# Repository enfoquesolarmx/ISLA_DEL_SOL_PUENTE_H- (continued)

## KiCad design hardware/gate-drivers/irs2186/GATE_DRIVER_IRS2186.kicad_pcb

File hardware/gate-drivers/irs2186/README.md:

# Módulo gate driver de medio puente H con IRS2186

**Proyecto:** Puente H — prototipo SPWM "Isla del Sol" (inversor 48 V → 127 V / 60 Hz, 1000 W; modo cargador 1 kVA)
**Módulo:** gate driver de **medio puente H** (una rama: MOSFET alto + MOSFET bajo) con bootstrap. Es el **módulo principal de producción**: bajo costo y 500 ns de tiempo muerto
**Intercambiable con:** UCC21520DW y TLP250 de trinchera (misma interfaz J1/J5, mismo firmware)
**Estado:** diseño terminado con P9 en J1; esquemático reordenado por bloques (2026-11-12). Pendiente: DRC final, fabricación y validación en banco
**Fecha:** 2026-11-03 (esquemático por bloques: 2026-11-12)
**Documentos relacionados:** [`docs/identificacion_dt_pin9.md`](../../../docs/identificacion_dt_pin9.md), [`docs/compensacion_adaptativa_tiempo_muerto.md`](../../../docs/compensacion_adaptativa_tiempo_muerto.md), [módulo TLP250](../tlp250-trinchera/README.md)

> Verificar los valores marcados con *(verificar)* contra el esquemático de KiCad antes de fabricar.

| Cara de componentes | Cara de soldadura |
| --- | --- |
|  |  |

*Esquemático por bloques (KiCad 9, hoja A4): **A** entrada J1 con R1/R2 y P9 · **B** alimentación de 15 V · **C** IRS2186 · **D** bootstrap · **E** salida J5 y NT1 · **F** reglas de firmware y compras. Cada bloque lleva su nota de diseño.*

*Izquierda: arriba, la bornera J1 de entrada (**P**9 · GND · L · GND · H); en medio, el IRS2186 (SOIC-8) con su desacoplo de 15 V (1 µF + 10 µF), la red de bootstrap (2.2 Ω 1 W + ES1D), el zener D6 de 18 V (1SMA5931BT3G), los capacitores de bootstrap (2 × 10 µF) y el electrolítico de respaldo de 15 V; abajo, el header J5 hacia el puente H (HO · VS1 · · · Gk · LO · G · 15V · llave). Derecha: la leyenda de seguridad **"ATENCIÓN: DT 500 ns MIN — VALIDAR MOSFET Y SW"**, la versión V.0.1.NOV.26.J.G y la **X** de la llave en la posición 8 de J5.*

---

## 1. Qué maneja este módulo

Cada módulo maneja **una rama** del puente H: el **MOSFET del lado alto** (HO, referido a VS, alimentado por bootstrap) y el **MOSFET del lado bajo** (LO, referido a COM).

```
            +48 V
              │
     HA ──► [MOSFET alto]          [MOSFET alto] ◄── HB
              │                         │
              ├── VS1 ──► transformador ◄── VS2 ──┤
              │                         │
     LA ──► [MOSFET bajo]          [MOSFET bajo] ◄── LB
              │                         │
             GND ───────────────────── GND
         └── módulo rama A ──┘    └── módulo rama B ──┘
```

- **El puente completo usa dos módulos iguales:** rama A (VS1) y rama B (VS2). En la rama B, "H" y "L" de J1 manejan HB y LB, y el pin "VS1" de J5 va a VS2.
- **Inversor (modulación híbrida):** rama A a **24 kHz**, rama B a **60 Hz**.
- **Cargador (unipolar):** las dos ramas a **24 kHz**.
- **Alcance:** **1 IRF100P219 por posición** (o hasta 2 IRF540N) con 500 ns. Para más carga de compuerta hace falta tótem rápido o el módulo UCC21520 (ver sección 6).

### Por qué el IRS2186

| Criterio | IRS2186 (este) | UCC21520DW | TLP250 + tótem |
| --- | --- | --- | --- |
| Costo y número de componentes | **El menor** ✓ | Medio | El mayor |
| Tiempo muerto | **500 ns** ✓ | 500 ns | 1 µs |
| Corriente de salida | 4 A / 4 A | 4 A / 6 A | ~2 A (más con tótem) |
| Aislamiento entrada / potencia | **No** (lógica referida a COM) | Sí | Sí |
| Reparación a mano | SOIC-8 | SOIC-16 ancho | DIP y TO-220 |

---

## 2. Interfaz

### 2.1 J1 — entrada, hacia la tarjeta de control (bornera de 5 terminales)

| Terminal | Señal | En este módulo |
| --- | --- | --- |
| 1 | H | HIN del IRS2186 (con 10 kΩ a GND) |
| 2 | GND | Tierra lógica = COM (trenzar con H) |
| 3 | L | LIN del IRS2186 (con 10 kΩ a GND) |
| 4 | GND | Tierra lógica = COM (trenzar con L) |
| **5** | **P9 — ID DT** | **Unido a GND** → el MCU usa **500 ns** |

- Serigrafía: "TRENZAR H Y L CON GND", etiquetas H / GND / L / GND / P9. Recomendado agregar **"OPERACION DT IRS2186=500NS"**.
- Las resistencias de 10 kΩ de HIN y LIN a GND mantienen los MOSFET apagados si la tarjeta de control no está conectada o el MCU está en reset.
- Si P9 queda con soldadura fría o cable suelto, el MCU lee 1 → **1 µs** (falla segura: funciona con más armónicos).

### 2.2 J5 — salida, hacia la tarjeta del puente H (header de 9 posiciones, 2.54 mm)

| Pin | Señal | Nota |
| --- | --- | --- |
| 1 | HO | Compuerta lado alto |
| 2 | VS1 | Fuente lado alto (nodo de conmutación) |
| 3 | — | Libre (separación del nodo conmutado) |
| 4 | GND_K | Retorno Kelvin del lado bajo |
| 5 | LO | Compuerta lado bajo |
| 6 | GND | Tierra de potencia |
| 7 | 15 V | Alimentación |
| 8 | — | **Llave mecánica:** sin pad; **quitar el pin 8 del header**; "X" en serigrafía |
| 9 | GND | Reservado (no se lee) |

### 2.3 Tierras: la entrada comparte la tierra de potencia

En el IRS2186 la lógica (HIN, LIN) va referida a **COM**, que también es el retorno del lado bajo. Por eso **el GND de J1 es la misma tierra de potencia**: el módulo no aísla la tarjeta de control.

Consecuencias y cuidados:

1. **Lazo de tierra:** el GND del cable J1 es un camino más entre la tarjeta de control y la potencia; con dos módulos (rama A y B) ya hay dos. Parte de la corriente de conmutación puede circular por esos cables.
2. **Rebote de tierra:** el di/dt del MOSFET bajo puede mover COM unos cientos de mV respecto al GND del MCU. El IRS2186 tiene umbrales de entrada de ~0.8 V / ~2.5 V *(verificar en la hoja de datos)*; con MCU a 5 V el margen es mayor.
3. **Medidas:**
   - **Par trenzado H/GND y L/GND, lo más corto posible.**
   - **Un solo punto de unión** entre tierra de control y tierra de potencia en la tarjeta del puente H (estrella), cerca de la fuente del MOSFET bajo o del shunt.
   - **Retorno de LO hacia GND_K** (Kelvin) y lógica hacia GND, unidos en un solo punto: la corriente de compuerta no debe pasar por la tierra de las entradas.
4. Si en banco aparecen disparos falsos o ruido en las entradas, los módulos **UCC21520** o **TLP250** lo eliminan por diseño (entrada aislada).

---

## 3. Circuito

### 3.1 IRS2186 (SOIC-8)

| Pin | Señal | Conexión |
| --- | --- | --- |
| 1 | HIN | J1-H, 10 kΩ a GND |
| 2 | LIN | J1-L, 10 kΩ a GND |
| 3 | COM | GND (tierra lógica y retorno del lado bajo) |
| 4 | LO | J5-5 |
| 5 | VCC | 15 V, con desacoplo a COM |
| 6 | VS | J5-2 (VS1) |
| 7 | HO | J5-1 |
| 8 | VB | VB1, nodo del bootstrap |

Verificar contra la hoja de datos de la variante comprada (IRS2186S, SOIC-8).

**Datos de la hoja de datos (Infineon IRS2186):** salida 4 A / 4 A; retardo de propagación ~170 ns típ., 250 ns máx.; diferencia entre canales ≤ 35 ns; VCC 10–20 V; offset VS hasta 600 V *(verificar)*.

### 3.2 Alimentación de 15 V (lado bajo)

- 15 V desde J5-7 a VCC, con desacoplo **10 µF + 1 µF X7R** pegados a los pines 5 y 3, más capacitor electrolítico de respaldo en la línea de 15 V *(verificar valores)*.
- **¿Por qué 15 V y no 12 V?** Más voltaje de compuerta (menor R_DS(on) y más margen de UVLO en el bootstrap de la rama de 60 Hz) dentro del rango de VCC del IRS2186 y del ±20 V de V_GS del MOSFET.

### 3.3 Bootstrap (lado alto)

```
15 V ── D5 (ES1D / ES1J) ── R9 2.2 Ω 1 W ──┬── VB1 (pin 8)
                                           ├── C2 + C9: 2 × 10 µF X7R 50 V 1206 ── VS1
                                           └── D6 zener 18 V (1SMA5931BT3G), cátodo a VB1 ── VS1
```

| Componente | Valor | Por qué |
| --- | --- | --- |
| R9 | 2.2 Ω, 1 W, **después del diodo** (entre el cátodo de D5 y VB1) | Limita el pico de recarga del bootstrap cuando VS cae a 0 V y, en esta posición, también la corriente de recuperación inversa de D5 cuando VS sube (IR Design Tip DT98-2; TI SLUA887A; patente US5969964, ya expirada). La resistencia en serie con el diodo cumple igual antes o después de él |
| D5 | ES1D (200 V) o **ES1J (600 V)** | Diodo **ultrarrápido** (no Schottky). ES1D limita el bus del módulo a ~120 V; con ES1J el límite lo ponen las separaciones del PCB (≤ 150 V) |
| C2, C9 | 2 × 10 µF X7R 50 V 1206 | Sostiene VB durante los **8.3 ms** de encendido continuo de la rama de 60 Hz. El X7R pierde capacidad con el voltaje DC: por eso dos |
| D6 | Zener 18 V (1SMA5931BT3G), cátodo a VB1 | Protege VB–VS contra picos por encima del máximo del IRS2186 |

**Reglas de firmware para el bootstrap:**
- **Precarga** de 0.5–2 ms con los lados bajos encendidos antes de arrancar el PWM.
- **Ciclo de trabajo máximo ≤ 95 %** en la rama de 24 kHz, para dejar tiempo de recarga en cada periodo.

### 3.4 Red de compuerta

Las resistencias de compuerta de cada MOSFET (arreglo R1/R2/R3) y las **10 kΩ de compuerta a fuente** están en la **tarjeta del puente H**, junto a cada MOSFET. El módulo solo entrega HO y LO.

---

## 4. Tiempo muerto: 500 ns

| Concepto | Valor |
| --- | --- |
| Diferencia de retardo entre canales del IRS2186 | ≤ 35 ns |
| Apagado del IRF100P219 en el peor caso (con la red de compuerta) | ~390 ns |
| **Piso de tiempo muerto** | **~390–425 ns → se usa 500 ns** |

- **Por qué no 1 µs siempre:** con 500 ns el 3er armónico es ~0.58 % y el THD ~0.81 %; con 1 µs, ~1.17 % y ~1.62 % (híbrida, 24 kHz, 1000 W, sin compensación).
- El tiempo muerto se aplica en **ambos flancos**, por firmware. El IRS2186 **no tiene tiempo muerto interno ni interbloqueo**: si el firmware enciende HIN y LIN a la vez, enciende los dos MOSFET.
- El MCU elige 500 ns **solo si P9 de los dos módulos está a GND** (ver `identificacion_dt_pin9.md`).

---

## 5. Layout

- **Dominio HV** (VB, VS1, HO, bootstrap, zener): **0.6 mm** al resto (regla `HV_a_LV`, IPC-2221 B2 para ≤ 150 V):
  ```
  (rule "HV_a_LV" (constraint clearance (min 0.6mm)) (condition "A.NetClass == 'HV' && B.NetClass != 'HV'"))
  ```
- Capacitores de bootstrap y zener **pegados a los pines 8 y 6** del IRS2186; desacoplo de VCC pegado a los pines 5 y 3.
- J1: P9 y las dos GND unidos a la zona de GND. Recomendado: *Thermal reliefs* en esos pads para soldar la bornera a mano sin soldaduras frías.
- J5: sin pad 8 (llave) con "X" en serigrafía.

---

## 6. Alcance: cantidad de MOSFET por posición

### 6.1 Criterio

Con 500 ns de tiempo muerto y ≤ 35 ns de diferencia entre canales del IRS2186, el **apagado del MOSFET (o de los MOSFET en paralelo) debe quedar en ~400 ns como máximo**. El tiempo de apagado crece con la **carga de compuerta total** que el IRS2186 (4 A, ~3.75 Ω equivalentes a 15 V) tiene que sacar.

Referencia: **1 × IRF100P219 (~240 nC a 15 V) → ~390 ns**. Eso fija el presupuesto en **~250 nC por posición** sin ayuda externa.

| Carga de compuerta a 15 V | IRF100P219 | IRF540N | Sin ayuda (IRS2186 solo) | Con tótem rápido (D44H11/D45H11 o ZXTC2062E6) |
| --- | --- | --- | --- | --- |
| ~100 nC | — | 1 | ✓ amplio | ✓ |
| ~200 nC | — | 2 | ✓ | ✓ |
| ~240 nC | 1 | — | ✓ **(diseño actual)** | ✓ |
| ~300 nC | — | 3 | ⚠ ~490 ns: solo con Qg típica, validar en banco | ✓ |
| ~400 nC | — | 4 | ✗ | ✓ validar en banco |
| ~480 nC | 2 | — | ✗ ~590 ns | ✓ ~280–320 ns |

*Qg a 15 V estimada: IRF100P219 ~240 nC (180 nC típ. a 10 V); IRF540N ~100 nC máx. (71 nC máx. a 10 V). Los tiempos son estimaciones con modelo RC; confirmarlos en banco.*

### 6.2 Potencia aproximada por configuración (48 V)

| MOSFET por posición | Potencia | Módulo recomendado |
| --- | --- | --- |
| **1 × IRF100P219** | **1000 W** | **IRS2186 (este)** ✓ |
| 2 × IRF100P219 | 1000 W más frío (pérdida por conducción ÷ 2 en total) | UCC21520, o IRS2186 + tótem rápido |
| 1 × IRF540N | ~300 W (cargas pequeñas: módem, celular, laptop) | IRS2186 ✓ |
| 2 × IRF540N | ~500 W | IRS2186 ✓ |
| 4 × IRF540N | ~800–1000 W | IRS2186 + tótem rápido, o UCC21520 |

Los MOSFET en paralelo deben ser **del mismo número de parte** (idealmente del mismo lote), cada uno con **su propia resistencia de compuerta** y layout simétrico. **No mezclar** IRF540N con IRF100P219 en la misma posición: con 1.7 mΩ contra 44 mΩ, el IRF100P219 lleva casi toda la corriente.

### 6.3 Si se necesitan más MOSFET que los que el IRS2186 maneja solo

1. **Usar el módulo UCC21520** (6 A de apagado, R_OL ~0.55 Ω): maneja 2 × IRF100P219 con 500 ns.
2. **Agregar al IRS2186 un tótem rápido** por canal: **D44H11/D45H11** (TO-220, 20 A pico, f_T 40–50 MHz) o **ZXTC2062E6** (SOT23-6, 20 V, 10 A pico). **No usar TIP41/42** (f_T 3 MHz: no mejora a un driver de 4 A) ni el ZXTC2061 (V_CEO 12 V < 15–18 V).
3. **PNP de descarga local por MOSFET** (solo acelera el apagado, que es el flanco crítico): emisor a la compuerta, colector a la fuente.
4. **Marcar el módulo** en la serigrafía con su alcance: "IRS2186 · 1 MOSFET/POSICION". Un IRS2186 sin tótem en un equipo de 2 MOSFET por posición declararía 500 ns (P9 a GND) **sin margen**.

### 6.4 Consumo y bootstrap con más MOSFET

- **Potencia de compuerta por canal:** Qg × V × f. Con 1 × IRF100P219 a 24 kHz: 240 nC × 15 V × 24 kHz ≈ **0.09 W**; con 2, ≈ 0.17 W. Se reparte entre el IRS2186, la red de compuerta y la R_G interna; dentro de lo que disipa el SOIC-8.
- **Bootstrap:** por pulso, ΔV = Qg / C_boot. Con 2 × 10 µF (~10–14 µF efectivos): 1 MOSFET → ~20 mV; 2 MOSFET → ~40 mV ✓.
- **Rama de 60 Hz (8.3 ms encendido):** las 10 kΩ de compuerta a fuente de la tarjeta del puente H consumen ~1.4 mA por MOSFET; con 2 MOSFET (5 kΩ) ≈ 2.8 mA → ~1.7–2.3 V de caída en los 8.3 ms, más la corriente propia del IRS2186. Verificar en banco que VB–VS1 quede con margen sobre el UVLO.

---

## 7. Validación en banco

1. **Sin MOSFET:** alimentar 15 V, verificar HO y LO con HIN/LIN en alto y bajo. Confirmar que con J1 desconectado las salidas quedan en bajo (10 kΩ).
2. **P9:** confirmar que el MCU reporta **500 ns**. Desconectar el cable P9 → debe reportar **1 µs**.
3. **Bootstrap:** medir VB–VS1 al final de los 8.3 ms de la rama de 60 Hz; debe quedar con margen sobre el UVLO del IRS2186.
4. **Tiempo muerto real:** medir en la compuerta de cada MOSFET el intervalo entre la bajada de LO y la subida de HO (y viceversa) → ≥ 500 ns.
5. **Ruido de tierra:** con carga, medir con el osciloscopio la diferencia entre GND del MCU y COM del módulo durante la conmutación; buscar disparos falsos en HIN/LIN.
6. **Armónicos:** 3er armónico ≈ 0.58 % a 1000 W sin compensación.

---

## 8. Bitácora

| Fecha | Qué se hizo | Resultado | Siguiente paso |
| --- | --- | --- | --- |
| 2026-11-03 | P9 en J1-5 unido a GND; J5 sin pad 8 con "X"; J5-9 a GND (reservado) | Módulo declara 500 ns ✓ | Serigrafía "OPERACION DT IRS2186=500NS", thermal reliefs en J1, DRC, fabricar |
| 2026-11-12 | Esquemático reordenado por bloques A–F con notas de diseño; J2 → **J1**, zener 1SMA5931B1 → **D6**, red D5-K → **VB1**; D5 con símbolo de diodo rápido (no Schottky); valores con voltaje y dieléctrico; J5-3 y J5-8 marcados sin conexión; PWR_FLAG en 15V y GND para el ERC; README corregido: R9 va **después** de D5 | Conexiones idénticas a la versión anterior (comparadas pin por pin). Referencias y nombre de red sincronizados en el PCB | En KiCad: Actualizar PCB desde esquemático (F8) para traer los valores nuevos, ERC y DRC |
| | | | |

---

## 9. Referencias

- Infineon, IRS2186(4)(S)PbF datasheet.
- International Rectifier, Design Tip DT98-2, "Bootstrap component selection for control ICs".
- International Rectifier, patente US5969964 (1999, expirada): resistencia en serie con el diodo de bootstrap.
- Texas Instruments, SLUA887A, "Bootstrap circuitry selection for half-bridge configurations".
- Infineon, IRF100P219 datasheet.
- IPC-2221 (separaciones eléctricas).

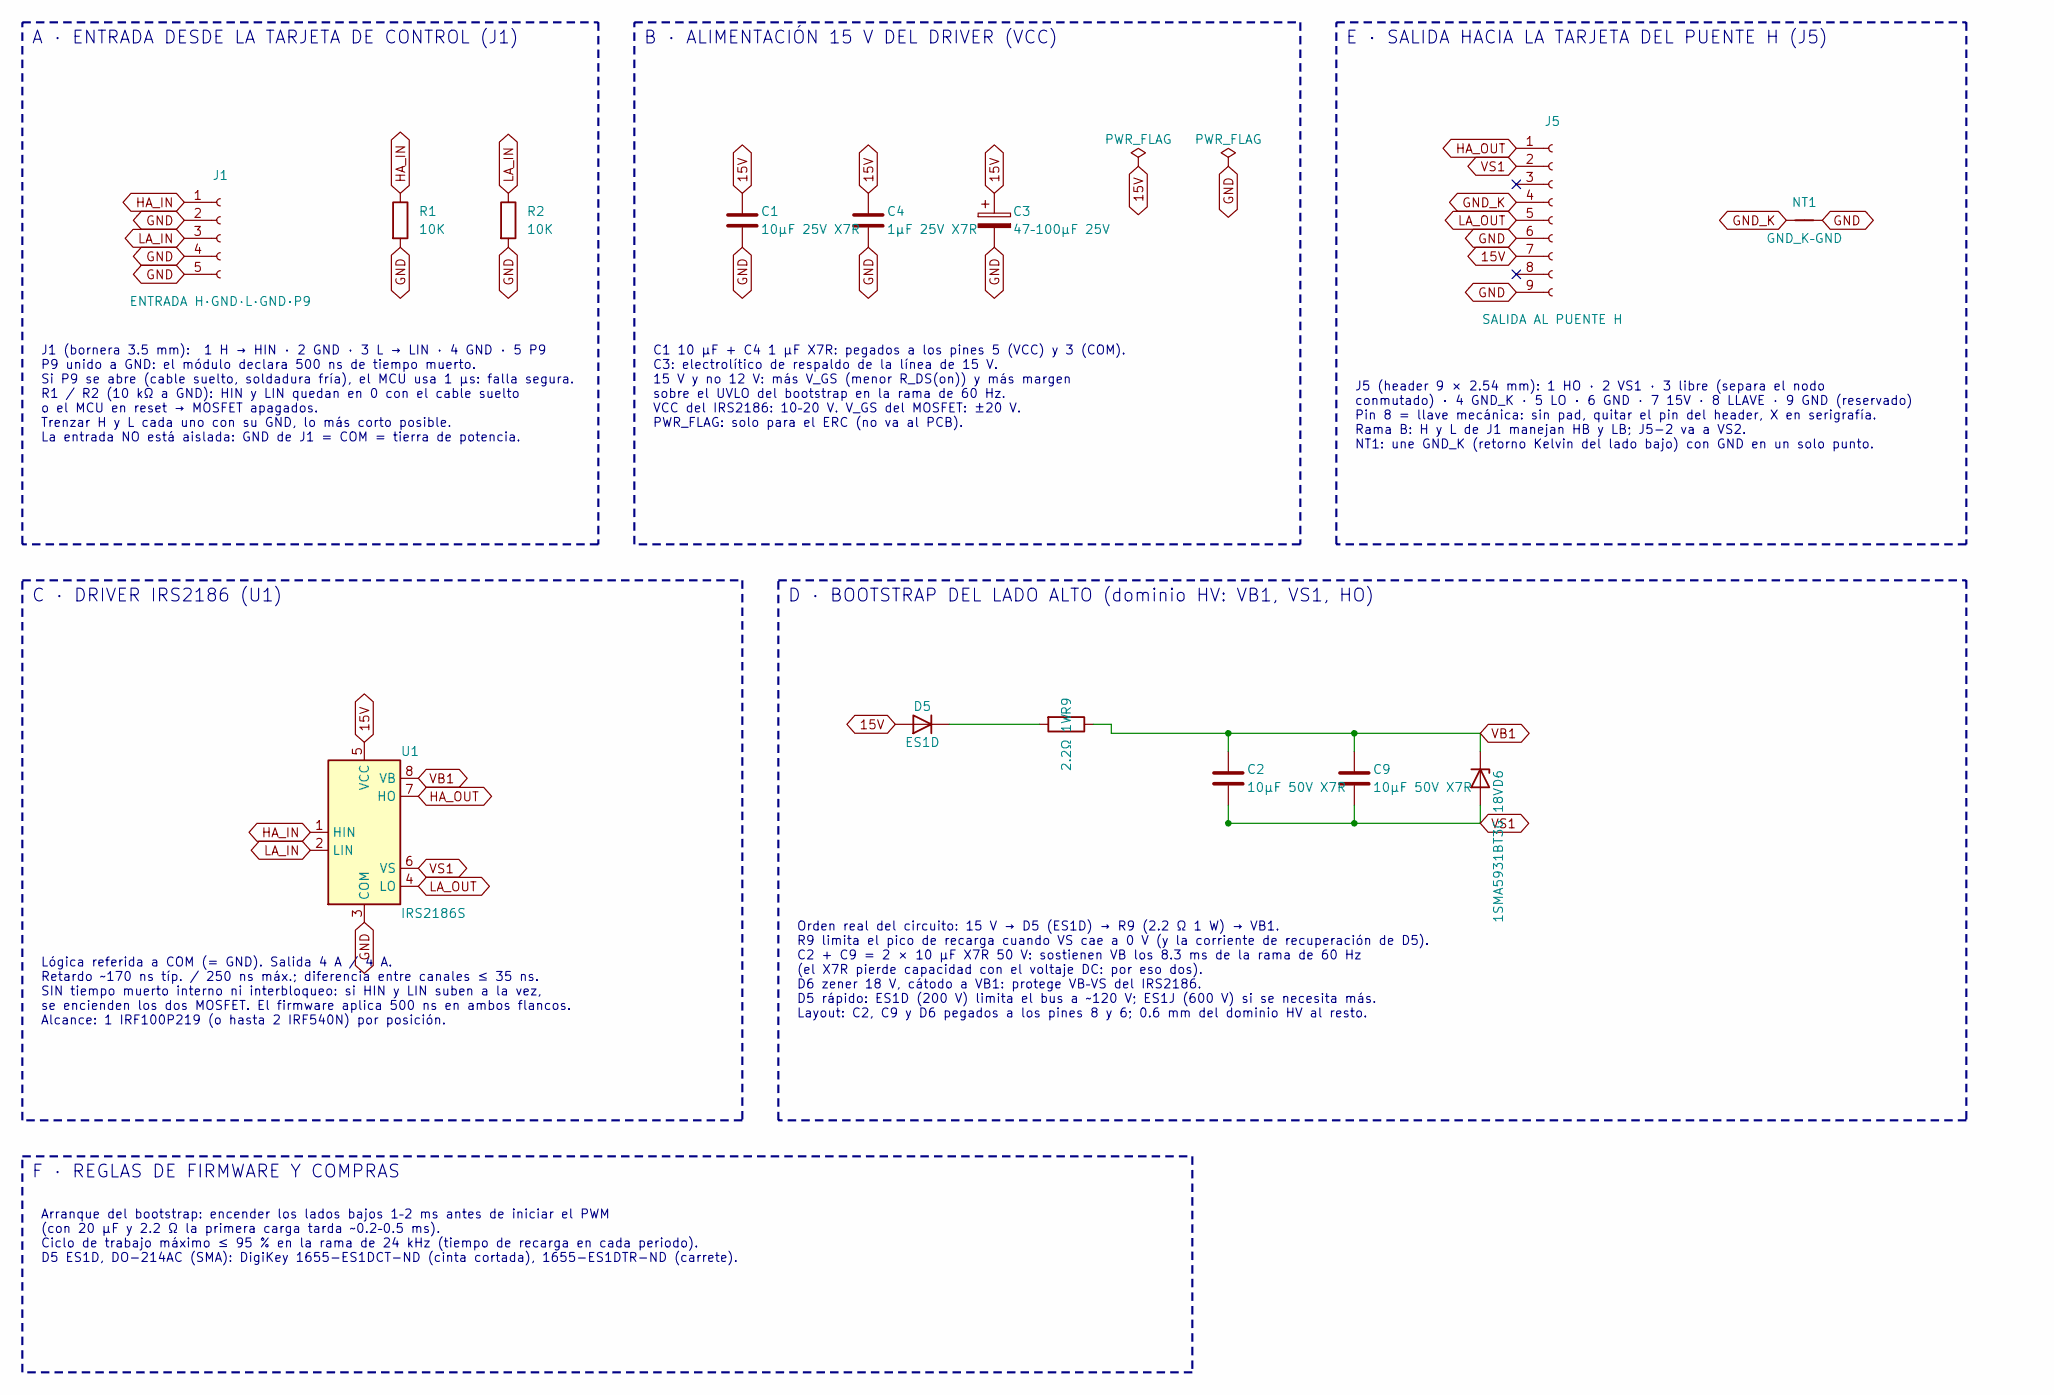
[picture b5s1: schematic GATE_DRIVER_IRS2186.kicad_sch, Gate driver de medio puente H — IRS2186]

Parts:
C1: 10µF 25V X7R; C_1206_3216Metric
C2, C9: 10µF 50V X7R; C_1206_3216Metric
C3: 47–100µF 25V; CP_Radial_D8.0mm_P3.50mm
C4: 1µF 25V X7R; C_1206_3216Metric
D5: ES1D; D_SMA
D6: 1SMA5931BT3G 18V; D_SMA
J1: ENTRADA H·GND·L·GND·P9; PhoenixContact_SPT_1.5_5-H-3.5_1x05_P3.5mm_Horizontal
J5: SALIDA AL PUENTE H; PinHeader_1x09_P2.54mm_Vertical
NT1: GND_K–GND; NetTie-2_SMD_Pad0.5mm
R1, R2: 10K; R_1206_3216Metric_Pad1.30x1.75mm_HandSolder
R9: 2.2Ω 1W; R_1210_3225Metric
U1: IRS2186S; SOIC-8_3.9x4.9mm_P1.27mm

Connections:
15V: C1.1, C3.1, C4.1, D5.2 (A), J5.7, U1.5 (VCC)
GND: C1.2, C3.2, C4.2, J1.2, J1.4, J1.5, J5.6, J5.9, NT1.2, R1.2, R2.2, U1.3 (COM)
GND_K: J5.4, NT1.1
HA_IN: J1.1, R1.1, U1.1 (HIN)
HA_OUT: J5.1, U1.7 (HO)
LA_IN: J1.3, R2.1, U1.2 (LIN)
LA_OUT: J5.5, U1.4 (LO)
unnamed: D5.1 (K), R9.2
VB1: C2.1, C9.1, D6.1 (K), R9.1, U1.8 (VB)
VS1: C2.2, C9.2, D6.2 (A), J5.2, U1.6 (VS)

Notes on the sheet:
A · ENTRADA DESDE LA TARJETA DE CONTROL (J1)
J1 (bornera 3.5 mm): 1 H → HIN · 2 GND · 3 L → LIN · 4 GND · 5 P9 P9 unido a GND: el módulo declara 500 ns de tiempo muerto. Si P9 se abre (cable suelto, soldadura fría), el MCU usa 1 µs: falla segura. R1 / R2 (10 kΩ a GND): HIN y LIN quedan en 0 con el cable suelto o el MCU en reset → MOSFET apaga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
B · ALIMENTACIÓN 15 V DEL DRIVER (VCC)
C1 10 µF + C4 1 µF X7R: pegados a los pines 5 (VCC) y 3 (COM). C3: electrolítico de respaldo de la línea de 15 V. 15 V y no 12 V: más V_GS (menor R_DS(on)) y más margen sobre el UVLO del bootstrap en la rama de 60 Hz. VCC del IRS2186: 10–20 V. V_GS del MOSFET: ±20 V. PWR_FLAG: solo para el ERC (no 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
E · SALIDA HACIA LA TARJETA DEL PUENTE H (J5)
J5 (header 9 × 2.54 mm): 1 HO · 2 VS1 · 3 libre (separa el nodo conmutado) · 4 GND_K · 5 LO · 6 GND · 7 15V · 8 LLAVE · 9 GND (reservado) Pin 8 = llave mecánica: sin pad, quitar el pin del header, X en serigrafía. Rama B: H y L de J1 manejan HB y LB; J5-2 va a VS2. NT1: une GND_K (retorno Kelvin de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
C · DRIVER IRS2186 (U1)
Lógica referida a COM (= GND). Salida 4 A / 4 A. Retardo ~170 ns típ. / 250 ns máx.; diferencia entre canales ≤ 35 ns. SIN tiempo muerto interno ni interbloqueo: si HIN y LIN suben a la vez, se encienden los dos MOSFET. El firmware aplica 500 ns en ambos flancos. Alcance: 1 IRF100P219 (o hasta 2 IR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
D · BOOTSTRAP DEL LADO ALTO (dominio HV: VB1, VS1, HO)
Orden real del circuito: 15 V → D5 (ES1D) → R9 (2.2 Ω 1 W) → VB1. R9 limita el pico de recarga cuando VS cae a 0 V (y la corriente de recuperación de D5). C2 + C9 = 2 × 10 µF X7R 50 V: sostienen VB los 8.3 ms de la rama de 60 Hz (el X7R pierde capacidad con el voltaje DC: por eso dos). D6 zener 18 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
F · REGLAS DE FIRMWARE Y COMPRAS
Arranque del bootstrap: encender los lados bajos 1–2 ms antes de iniciar el PWM (con 20 µF y 2.2 Ω la primera carga tarda ~0.2–0.5 ms). Ciclo de trabajo máximo ≤ 95 % en la rama de 24 kHz (tiempo de recarga en cada periodo). D5 ES1D, DO-214AC (SMA): DigiKey 1655-ES1DCT-ND (cinta cortada), 1655-ES1D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

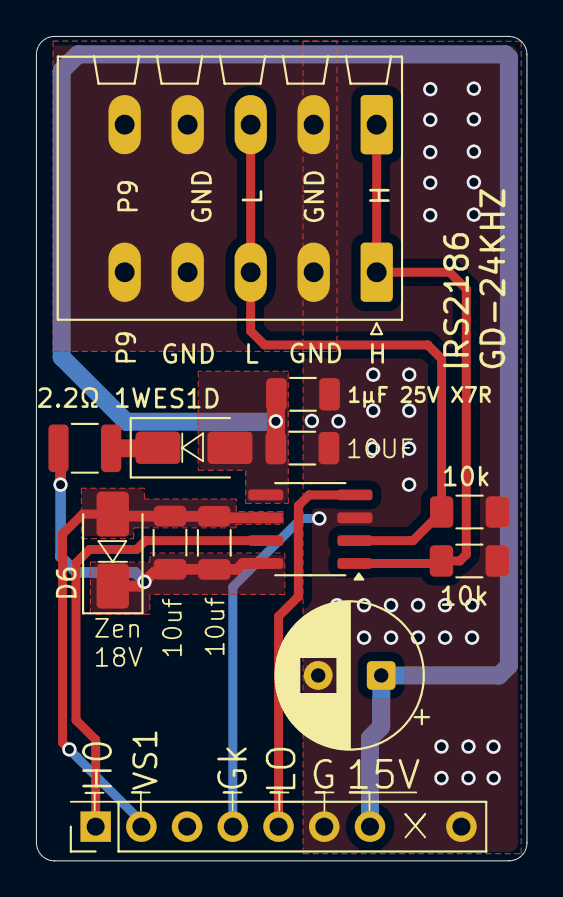
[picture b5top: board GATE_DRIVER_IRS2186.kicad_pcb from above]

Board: 2 copper layers, 27.2 x 45.8 mm, 14 parts (1 on the bottom side), 10 nets.

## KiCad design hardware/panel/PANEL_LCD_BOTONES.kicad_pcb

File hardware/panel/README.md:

# Panel frontal V0.2: pantalla LCD I2C y 4 botones

El panel frontal es **la cara del inversor**. Sirve para dos cosas:
- **ver todos los datos** que miden las tarjetas: red, salida, batería, potencia, temperatura, protecciones y estado de los relés;
- **configurar el inversor** desde el menú del **SETUP**, entre otras cosas el modo **INVERSOR CASA / INVERSOR CARGA (UPS)**, que decide la unión N–PE (DC-019).

Se conecta con un solo cable de 5 hilos a **J7 de la [tarjeta de control](../control/README.md)**. Lo maneja el microcontrolador **AUX**. El CRÍTICO mide y protege, y el AUX solo muestra y pide cambios. **Si el panel se desconecta o se cuelga, el inversor sigue funcionando y protegiendo igual.**

> **Para quien arma y repara en la trinchera:** igual que en las otras tarjetas, cada bloque dice **qué hace**, **por qué tiene ese valor** y **qué pasa si falla**. Antes de fabricar, revisa la sección [6. Verificar antes de fabricar](#6-verificar-antes-de-fabricar): la posición del zócalo del módulo I2C se mide con el módulo real.

*PCB V0.2 de 116 × 100 mm, 2 capas. Dorado = cobre de arriba (F.Cu), azul = cobre de abajo (B.Cu). Se ven las dos siluetas (LCD 20×4 por fuera y 16×2 por dentro), el zócalo J2 del módulo I2C, la botonera B1–B4 y J1 hacia la tarjeta de control.*

*Esquemático por bloques (KiCad 9, hoja A4): A conector a la tarjeta de control, B pantalla y módulo I2C, C botonera, D montaje.*

---

## 0. Mapa del panel

| # | Bloque | Componentes | En una frase |
| --- | --- | --- | --- |
| 1 | [Conector a la tarjeta de control](#1-conector-a-la-tarjeta-de-control-j1--j7) | J1, C1 | Un cable 1:1 de 5 hilos: I2C, 5 V, GND y botonera |
| 2 | [Pantalla y módulo I2C](#2-pantalla-lcd-y-módulo-i2c-j2) | J2, C2 | El módulo PCF8574 entra **directo** al zócalo, sin cables |
| 3 | [Botonera](#3-botonera-4-botones-en-un-solo-pin) | SW1–SW4, R1–R4, C3 | 4 botones en un solo pin analógico (A7 del AUX) |
| 4 | [Montaje mecánico](#4-montaje-mecánico-162-o-204) | H1–H11 | La misma placa sirve para LCD 16×2 o 20×4 |
| 5 | [Qué muestra y qué configura](#5-qué-muestra-y-qué-configura-propuesta-de-firmware) | Firmware del AUX | Pantallas de datos y menú SETUP |

---

## 1. Conector a la tarjeta de control (J1 ↔ J7)

| J1 | Señal | Va a (tarjeta de control) | Notas |
| --- | --- | --- | --- |
| 1 | SCL_LCD | D5 del AUX | I2C por software, **en un bus aparte** del enlace CRÍTICO–AUX: si la pantalla se cuelga, no tumba el enlace |
| 2 | SDA_LCD | D4 del AUX | — |
| 3 | 5V | Riel de 5 V (7805) | Pantalla, luz de fondo y botonera |
| 4 | GND | GND | Retorno común |
| 5 | BOTON_LCD | A7 del AUX, con **R42 = 10 kΩ a 5 V** | El pull-up está **en la tarjeta de control**, no aquí |

| Ref. | Valor | Qué hace | Por qué |
| --- | --- | --- | --- |
| **J1** | Tira macho 1×5, 2.54 mm, **a 90°** | Sale por el canto derecho | Vertical, con el conector del cable puesto, mediría ~22 mm y chocaría con el frente |
| **C1** | 10 µF electrolítico (5 mm) | Reserva a la entrada del cable | La luz de fondo pide corriente en picos; el cable tiene resistencia e inductancia |

- **Cable:** 5 hilos, **pin n con pin n** (1:1). Trenza BOTON_LCD con GND. Largo recomendado: menos de 50 cm.
- **Si el cable se suelta:** A7 queda en 5 V por R42 = "ningún botón". La pantalla se apaga y **el inversor no cambia de estado**.

---

## 2. Pantalla LCD y módulo I2C (J2)

La pantalla usa el módulo adaptador **PCF8574** (FC-113 o equivalente) soldado atrás del LCD. Sus 4 pines salen **rectos, perpendiculares al módulo**, apuntando hacia esta placa. Por eso entran **directo en el zócalo J2**: el LCD se monta en sus postes y queda conectado, sin cables.

| J2 | Señal | Pin del módulo PCF8574 |
| --- | --- | --- |
| 1 (cuadrado) | GND | GND |
| 2 | 5V | VCC |
| 3 | SDA_LCD | SDA |
| 4 | SCL_LCD | SCL |

| Ref. | Valor | Qué hace | Por qué |
| --- | --- | --- | --- |
| **J2** | Tira **hembra** 1×4, 2.54 mm, vertical (8.5 mm) | Recibe los pines del módulo I2C | Desmontable: la pantalla se cambia sin soldar |
| **C2** | 100 nF cerámico | Desacople pegado al zócalo | Filtra el ruido de alta frecuencia del PCF8574. **Bajo (≤ 5 mm):** queda debajo del módulo |

- **Orden de pines:** casi todos los módulos traen GND · VCC · SDA · SCL. **Revisa la serigrafía del tuyo** antes de montarlo: si viene en otro orden, el 5 V queda al revés.
- **Dirección I2C:** típica **0x27** (PCF8574T) o **0x3F** (PCF8574AT). El firmware la busca sola al arrancar (ver la sección 5).
- **Contraste:** potenciómetro azul del módulo. Si la pantalla prende pero no muestra nada, casi siempre es el contraste.
- **Luz de fondo:** el puente (jumper) del módulo la habilita. El firmware la puede apagar después de un rato sin tocar botones.
- **Pull-ups del I2C:** la mayoría de los módulos traen sus resistencias de pull-up en SDA y SCL. Si el tuyo no las trae, agrega 4.7 kΩ a 5 V en cada línea.

---

## 3. Botonera: 4 botones en un solo pin

Cada botón conecta BOTON_LCD a GND **con su propia resistencia, en paralelo** (no en cadena: si una falla, solo falla ese botón). Con R42 = 10 kΩ en la tarjeta de control se forma un divisor: **V = 5 V × Rb / (10 kΩ + Rb)**.

| Botón | Resistencia (E24) | Voltaje en A7 | Cuentas ADC | Función propuesta |
| --- | --- | --- | --- | --- |
| Ninguno | — | 5.00 V | 1023 | — |
| **B1** | R1 = **2.4 kΩ** | 0.97 V | ~198 | **ATRÁS / ESC** |
| **B2** | R2 = **6.8 kΩ** | 2.02 V | ~414 | **ARRIBA / −** |
| **B3** | R3 = **15 kΩ** | 3.00 V | ~614 | **ABAJO / +** |
| **B4** | R4 = **39 kΩ** | 3.98 V | ~815 | **OK / ENTRAR** (sostenido 3 s: SETUP) |

| Ref. | Valor | Qué hace | Por qué |
| --- | --- | --- | --- |
| **SW1–SW4** | Botón táctil THT 6 × 6 mm | Cierra BOTON_LCD a GND por su resistencia | La huella es la misma para cualquier altura de actuador: se elige según el frente (sección 4) |
| **R1–R4** | 2.4 k / 6.8 k / 15 k / 39 k, ¼ W, 1 % de preferencia | Fijan el voltaje de cada botón | Separación de ~1 V entre botones: tolera resistencias de 5 % y ruido sin confundir un botón con otro. Corriente máxima: 0.4 mA |
| **C3** | 100 nF, **opcional (DNP)** | Filtro de la línea | Solo si el cable es largo o hay ruido. De entrada no se coloca |

- **Firmware:** umbrales en 0.5 / 1.5 / 2.5 / 3.5 / 4.5 V (~102 / 307 / 512 / 716 / 921 cuentas). Antirrebote: 3 o 4 lecturas iguales (~30 ms). Con dos botones oprimidos a la vez se lee el de menor número.
- **No cambies R42** en la tarjeta de control: todos los voltajes dependen de ella.
- **Prueba con multímetro** (panel conectado, sin pantalla): mide BOTON_LCD contra GND y oprime cada botón; debe dar la columna "Voltaje en A7" con ±0.1 V.

---

## 4. Montaje mecánico: 16×2 o 20×4

La misma placa acepta **las dos pantallas**. Ambas se alinean por el **pin 1 de su conector de 16 pines**. Como el módulo I2C va soldado en ese conector, sus pines caen **en el mismo lugar** con cualquiera de las dos, y J2 sirve para ambas.

| Ref. | Para | Medida | Notas |
| --- | --- | --- | --- |
| **H1** | LCD 16×2 **y** 20×4 | Ranura M3 de 7.2 × 3.2 mm | Esquina superior izquierda: los barrenos de las dos pantallas se enciman y comparten la ranura |
| **H2–H4** | LCD 16×2 (80 × 36 mm) | Ranuras M3 de 5.2 × 3.2 mm, a 75 × 31 mm entre centros | — |
| **H5–H7** | LCD 20×4 (98 × 60 mm) | Ranuras M3 de 5.2 × 3.2 mm, a 93 × 55 mm entre centros | — |
| **H8–H11** | Fijación al gabinete | Barrenos M3 en las esquinas | — |

- **Ranuras de ±1 mm:** absorben la diferencia entre marcas de pantalla. Las ranuras son huellas propias, en la librería `Isla_del_Sol.pretty` que viene con el proyecto (`fp-lib-table`).
- **Pila de alturas:** los postes del LCD fijan a qué altura quedan los pines I2C. Para que entren unos 3 mm en el zócalo de 8.5 mm:

  **Altura del poste ≈ (cara trasera del LCD a la punta de los pines I2C) + 5.5 mm**

  Con los módulos comunes salen postes de **15 a 18 mm**.
- **Botones:** con esa pila, el frente del LCD queda a **~25 mm** de la placa. Elige el actuador de los botones según la altura que midas, o usa capuchones extensores.
- **Nada alto bajo el módulo I2C:** la sombra del módulo está dibujada en la capa Dwgs.User. Ahí solo va C2 (bajo). C1 (alto) va junto a J1.
- **Ventana del panel:** se corta a la medida del vidrio del LCD (16×2: ~71 × 24 mm; 20×4: ~77 × 26 mm).

---

## 5. Qué muestra y qué configura (propuesta de firmware)

> **Estado:** el hardware ya está listo. Las pantallas y el menú de esta sección son la **propuesta para el firmware del AUX**. Se ajustarán cuando se programe y se valide en banco.

### Datos disponibles

Todos los mide la tarjeta de control (el CRÍTICO por sus pines, el AUX por CAN y por su monitor) y el AUX los recibe por el enlace I2C entre los dos.

| Dato | De dónde sale | Pantalla |
| --- | --- | --- |
| Voltaje de salida del inversor (V AC) | A0 del CRÍTICO (sensado AC del inversor) | `SAL 127V` |
| Voltaje de la red (V AC) y si hay red | A6 del CRÍTICO (sensado AC de la red) | `RED 125V` / `RED --` |
| Frecuencia (Hz) | Cruces por cero de A0 / A6 | `60.0Hz` |
| Corriente AC (A) y potencia (W / VA) | A2 del CRÍTICO, pinza SCT-013-015 | `5.2A 640W` |
| Voltaje de batería (V DC) | A3 del CRÍTICO | `BAT 51.2V` |
| Estado de carga y límites de la batería | CAN con el BMS (AUX) | `SOC 78%` |
| Temperatura del puente H (°C) | A1 del CRÍTICO, NTC 10 k | `T 42C` |
| Riel de 15 V | A1 del AUX (monitor del riel) | `15V OK` |
| Modo de trabajo | SETUP | `CASA` / `UPS` |
| Fuente de la casa | Órdenes a la tarjeta de transferencia (J15) | `RED` / `INV` / `CARGANDO` |
| Unión N–PE | TN_CMD (solo en modo CASA con inversor) | `TN` |
| Permiso del inversor | EN_SENSE (EN_HW leído en D8) | `ON` / `OFF` |
| Protecciones | SENSOR_OK, I_LIM, sobretemperatura, batería baja | Pantalla de alarma |

### Pantallas de datos (B2 / B3 cambian de pantalla)

**LCD 16×2:**

```
+----------------+     +----------------+     +----------------+
|INV 127V  60.0Hz|     |BAT 51.2V SOC78%|     |T 42C  15V OK   |
|5.2A  640W  CASA|     |CARGA  +8.0A    |     |RED 125V  TN    |
+----------------+     +----------------+     +----------------+
  1. Salida              2. Batería             3. Estado
```

**LCD 20×4:** cabe todo en una sola pantalla.

```
+--------------------+
|INV 127V 60.0Hz CASA|
|5.2A  640W   T 42C  |
|BAT 51.2V  SOC 78%  |
|RED 125V  TN  15V OK|
+--------------------+
```

**Alarma:** tiene prioridad sobre cualquier pantalla, parpadea la luz de fondo y suena el buzzer de la tarjeta de control.

```
+----------------+
|! SOBRECORRIENTE|
|B1: ver  B4: ok |
+----------------+
```

### Menú SETUP (B4 sostenido 3 s)

| Opción | Valores | Qué hace | Candado propuesto |
| --- | --- | --- | --- |
| **Modo de trabajo** | INVERSOR CASA / INVERSOR CARGA (UPS) | CASA: el inversor alimenta la casa y **se une N–PE** (TN). UPS: alimenta una carga y **no se une** (DC-019) | **Solo con el inversor apagado** (EN_HW = 0) y confirmando con B4 |
| **Pantalla** | 16×2 / 20×4 | Acomoda los datos al tamaño | — |
| **Luz de fondo** | Siempre / 1 min / 5 min | Ahorra energía de la batería | — |
| **Diagnóstico** | Solo lectura | Lecturas crudas del ADC, dirección I2C detectada, versión de firmware | — |
| **Salir** | — | Guarda en EEPROM y regresa a los datos | — |

- **Navegación:** B2/B3 suben y bajan; B4 entra o confirma; B1 regresa sin guardar.
- **La seguridad no depende del menú.** El panel solo **pide** cambios. Los candados de verdad están por hardware: Q1/Q2 de la tarjeta de transferencia, el corte del PWM y la caída automática a la red.
- **Arranque:** el firmware busca la pantalla en 0x27 y en 0x3F. Si no la encuentra, el inversor trabaja igual y lo reporta por el buzzer.

---

## 6. Verificar antes de fabricar

1. **Posición del zócalo J2.** No hay un plano estándar del módulo FC-113. La V0.2 supone el pin GND del módulo a **2.0 mm a la izquierda y 5.0 mm abajo del pin 1 del LCD** (vista de frente). **Mídelo en tu módulo.** Si es distinto, en KiCad mueve J2 y vuelve a rutear sus 4 pistas cortas.
2. **Pin 1 de cada pantalla.** Se supuso el pin 1 a 8.0 mm (16×2) y 10.0 mm (20×4) del borde izquierdo, y a 2.5 mm del borde de arriba. Las ranuras de ±1 mm absorben la diferencia, pero compruébalo con tu pantalla.
3. **Orden de pines del módulo I2C** (GND · VCC · SDA · SCL).
4. **Altura de los postes y de los botones** (sección 4).
5. **En KiCad:** presiona **B** para rellenar la zona de GND (B.Cu) y corre el DRC.

## 7. Ensamble

1. Suelda R1–R4, C2 y C3 (si lo usas), luego J2, C1, los botones y al final J1.
2. Sin pantalla, conecta el cable a J7 y mide: 5 V entre J2-2 y J2-1; BOTON_LCD con cada botón (tabla de la sección 3).
3. Monta los postes en el LCD, presenta el módulo en J2 y atornilla.
4. Ajusta el contraste.

## 8. Lista de materiales

| Ref. | Cant. | Descripción |
| --- | --- | --- |
| J1 | 1 | Tira macho 1×5, 2.54 mm, a 90° |
| J2 | 1 | Tira hembra 1×4, 2.54 mm, vertical 8.5 mm |
| C1 | 1 | Electrolítico 10 µF, ≥ 16 V, 5 mm, paso 2 mm |
| C2 | 1 | Cerámico 100 nF, paso 2.5 mm, bajo |
| C3 | 0–1 | Cerámico 100 nF (opcional) |
| R1–R4 | 4 | 2.4 k, 6.8 k, 15 k, 39 k, ¼ W (DIN0204) |
| SW1–SW4 | 4 | Botón táctil 6 × 6 mm THT, actuador según la altura del frente |
| — | 1 | LCD 16×2 o 20×4 con módulo PCF8574 (pines rectos) |
| — | 4 | Postes M3 hembra-hembra (15–18 mm según la medición) + tornillos |
| — | 4 | Postes M3 para fijar al gabinete + tornillos |
| — | 1 | Cable de 5 hilos 1:1 con conectores Dupont hembra (< 50 cm) |

## 9. Archivos

| Archivo | Contenido |
| --- | --- |
| `PANEL_LCD_BOTONES.kicad_pro` / `.kicad_sch` / `.kicad_pcb` | Proyecto KiCad 9 |
| `fp-lib-table` + `Isla_del_Sol.pretty/` | Huellas propias: ranuras M3 de 5.2 y 7.2 mm |
| `img/` | Vista del PCB y del esquemático |

## 10. Historial

| Versión | Fecha | Cambios |
| --- | --- | --- |
| V0.1 | 2026-11-11 | LCD 16×2 con cable Dupont al módulo I2C, J1/J2 a 90°, 100 × 80 mm |
| **V0.2** | 2026-11-11 | **LCD 16×2 o 20×4** en la misma placa; **módulo I2C directo a zócalo** (J2 hembra vertical); ranuras de ±1 mm; C1 a la entrada del cable; 116 × 100 mm |

## 11. Pendientes

- [ ] Medir el módulo I2C real y ajustar la posición de J2 (sección 6).
- [ ] Definir la altura de los postes y de los botones con el gabinete.
- [ ] Firmware del AUX: pantallas, menú SETUP, detección de dirección I2C y candado del modo con el inversor apagado.
- [ ] Fabricar y validar en banco con la tarjeta de control.

## Ver también

- [Tarjeta de control V0.1](../control/README.md), módulo 18 (J7, R42 y la botonera).
- [Tarjeta de transferencia de carga V0.1](../transferencia_reles/README.md) (modos CASA / UPS y unión N–PE).
- [Decisiones críticas](../../docs/decisiones_criticas.md), DC-019.

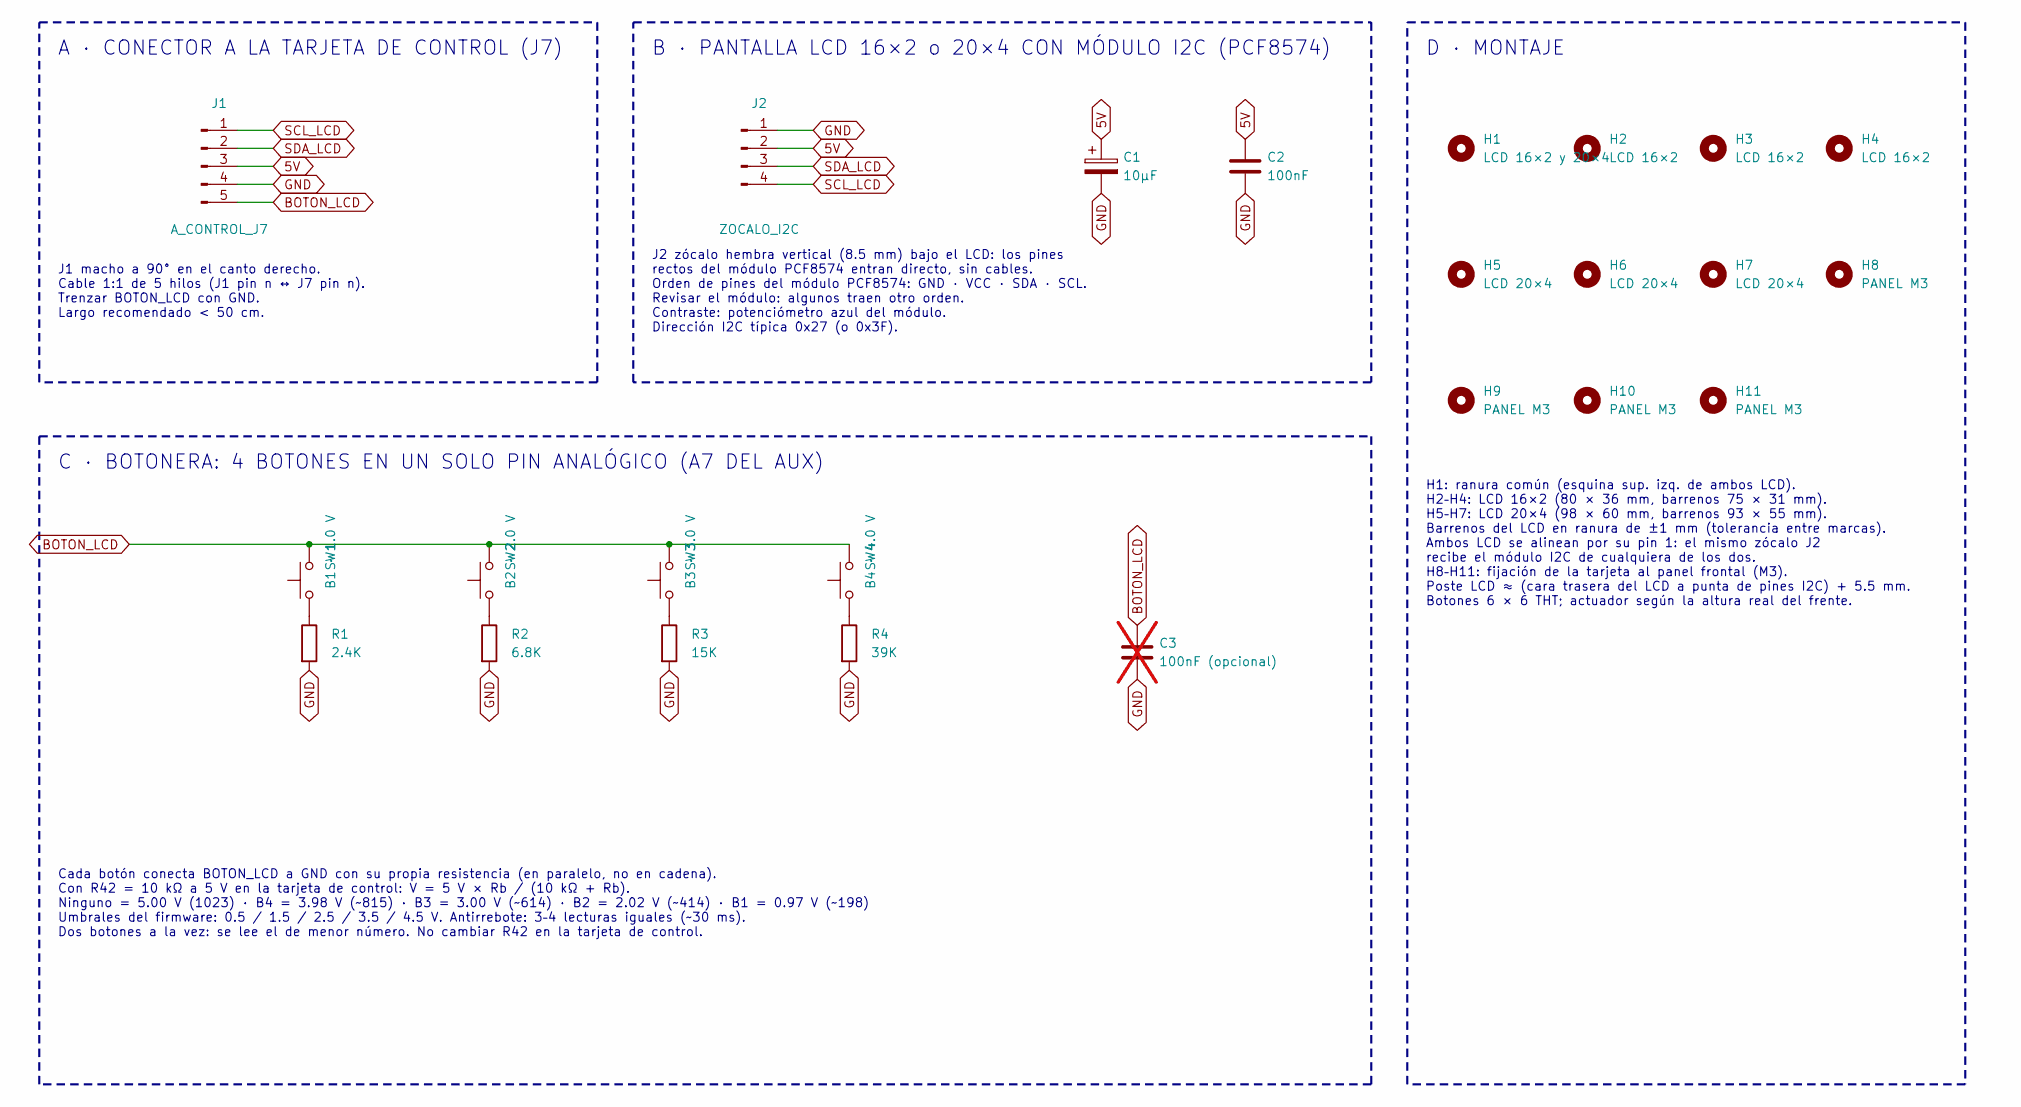
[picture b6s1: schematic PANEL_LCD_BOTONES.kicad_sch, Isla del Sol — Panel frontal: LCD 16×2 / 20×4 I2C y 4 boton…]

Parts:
C1: 10µF; CP_Radial_D5.0mm_P2.00mm
C2: 100nF; C_Disc_D3.0mm_W2.0mm_P2.50mm
C3: 100nF (opcional); C_Disc_D3.0mm_W2.0mm_P2.50mm; not fitted
H1: LCD 16×2 y 20×4; Ranura_M3_7.2x3.2
H2, H3, H4: LCD 16×2; Ranura_M3_5.2x3.2
H5, H6, H7: LCD 20×4; Ranura_M3_5.2x3.2
H8, H9, H10, H11: PANEL M3; MountingHole_3.2mm_M3
J1: A_CONTROL_J7; PinHeader_1x05_P2.54mm_Horizontal
J2: ZOCALO_I2C; PinSocket_1x04_P2.54mm_Vertical
R1: 2.4K; R_Axial_DIN0204_L3.6mm_D1.6mm_P5.08mm_Horizontal
R2: 6.8K; R_Axial_DIN0204_L3.6mm_D1.6mm_P5.08mm_Horizontal
R3: 15K; R_Axial_DIN0204_L3.6mm_D1.6mm_P5.08mm_Horizontal
R4: 39K; R_Axial_DIN0204_L3.6mm_D1.6mm_P5.08mm_Horizontal
SW1: B1 · 1.0 V; SW_PUSH_6mm_H13mm
SW2: B2 · 2.0 V; SW_PUSH_6mm_H13mm
SW3: B3 · 3.0 V; SW_PUSH_6mm_H13mm
SW4: B4 · 4.0 V; SW_PUSH_6mm_H13mm

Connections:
5V: C1.1, C2.1, J1.3, J2.2
BOTON_LCD: C3.1, J1.5, SW1.2, SW2.2, SW3.2, SW4.2
GND: C1.2, C2.2, C3.2, J1.4, J2.1, R1.2, R2.2, R3.2, R4.2
unnamed: R1.1, SW1.1
unnamed: R2.1, SW2.1
unnamed: R3.1, SW3.1
unnamed: R4.1, SW4.1
SCL_LCD: J1.1, J2.4
SDA_LCD: J1.2, J2.3

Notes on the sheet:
A · CONECTOR A LA TARJETA DE CONTROL (J7)
J1 macho a 90° en el canto derecho. Cable 1:1 de 5 hilos (J1 pin n ↔ J7 pin n). Trenzar BOTON_LCD con GND. Largo recomendado < 50 cm.
B · PANTALLA LCD 16×2 o 20×4 CON MÓDULO I2C (PCF8574)
J2 zócalo hembra vertical (8.5 mm) bajo el LCD: los pines rectos del módulo PCF8574 entran directo, sin cables. Orden de pines del módulo PCF8574: GND · VCC · SDA · SCL. Revisar el módulo: algunos traen otro orden. Contraste: potenciómetro azul del módulo. Dirección I2C típica 0x27 (o 0x3F).
C · BOTONERA: 4 BOTONES EN UN SOLO PIN ANALÓGICO (A7 DEL AUX)
Cada botón conecta BOTON_LCD a GND con su propia resistencia (en paralelo, no en cadena). Con R42 = 10 kΩ a 5 V en la tarjeta de control: V = 5 V × Rb / (10 kΩ + Rb). Ninguno = 5.00 V (1023) · B4 = 3.98 V (~815) · B3 = 3.00 V (~614) · B2 = 2.02 V (~414) · B1 = 0.97 V (~198) Umbrales del firmware: 0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
D · MONTAJE
H1: ranura común (esquina sup. izq. de ambos LCD). H2–H4: LCD 16×2 (80 × 36 mm, barrenos 75 × 31 mm). H5–H7: LCD 20×4 (98 × 60 mm, barrenos 93 × 55 mm). Barrenos del LCD en ranura de ±1 mm (tolerancia entre marcas). Ambos LCD se alinean por su pin 1: el mismo zócalo J2 recibe el módulo I2C de cualq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

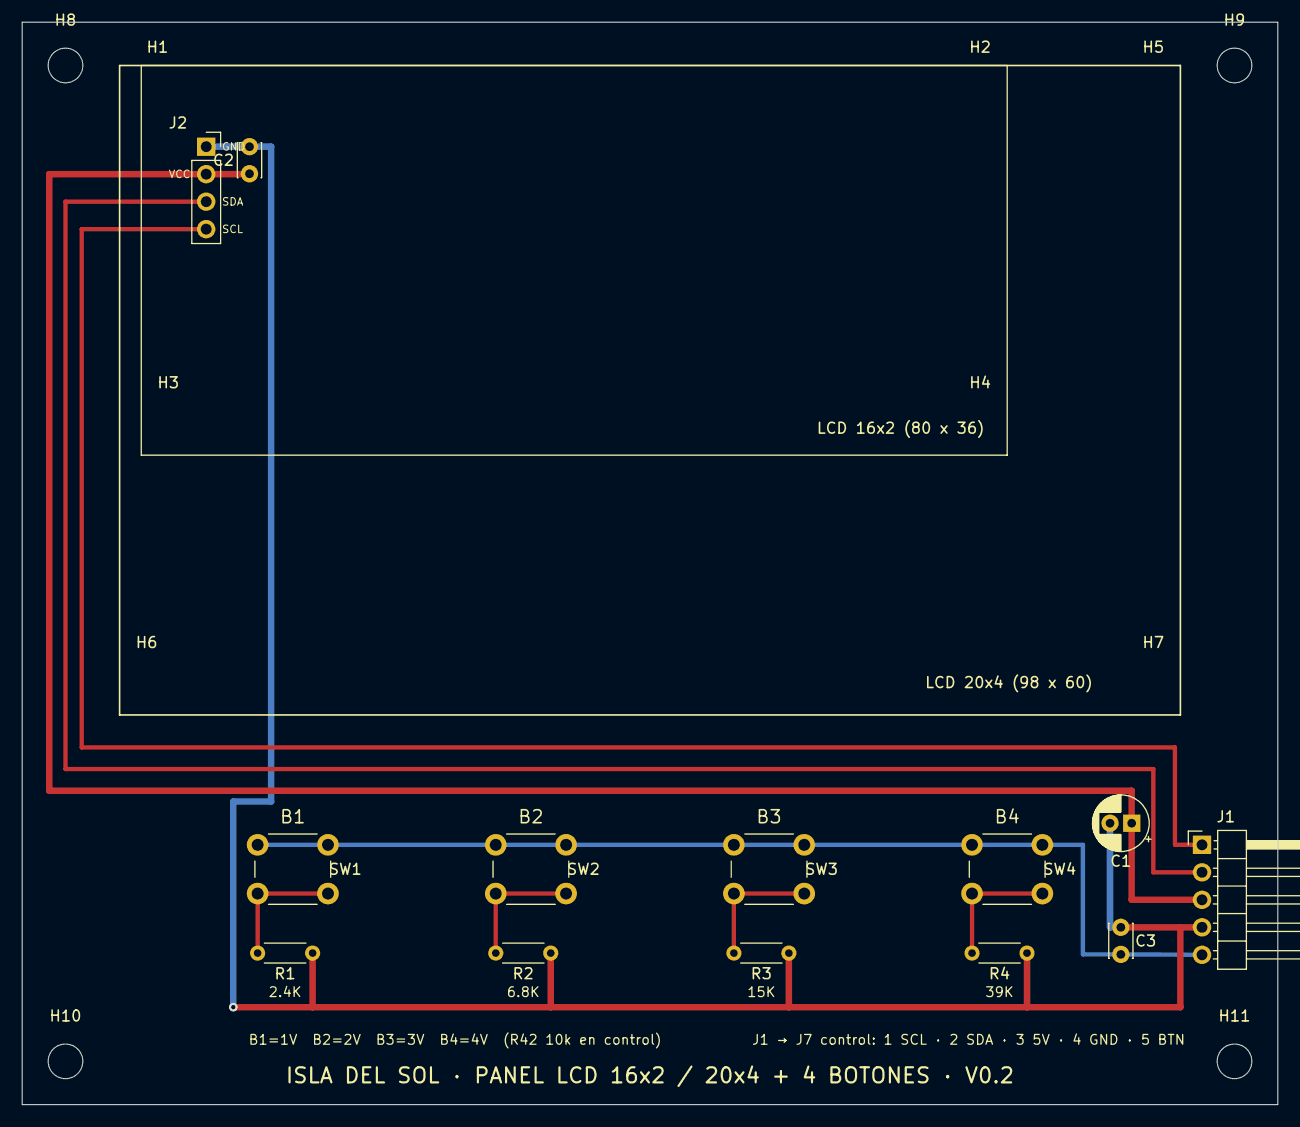
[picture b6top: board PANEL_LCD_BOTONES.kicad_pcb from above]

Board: 2 copper layers, 116.0 x 100.0 mm, 24 parts (0 on the bottom side), 9 nets.
